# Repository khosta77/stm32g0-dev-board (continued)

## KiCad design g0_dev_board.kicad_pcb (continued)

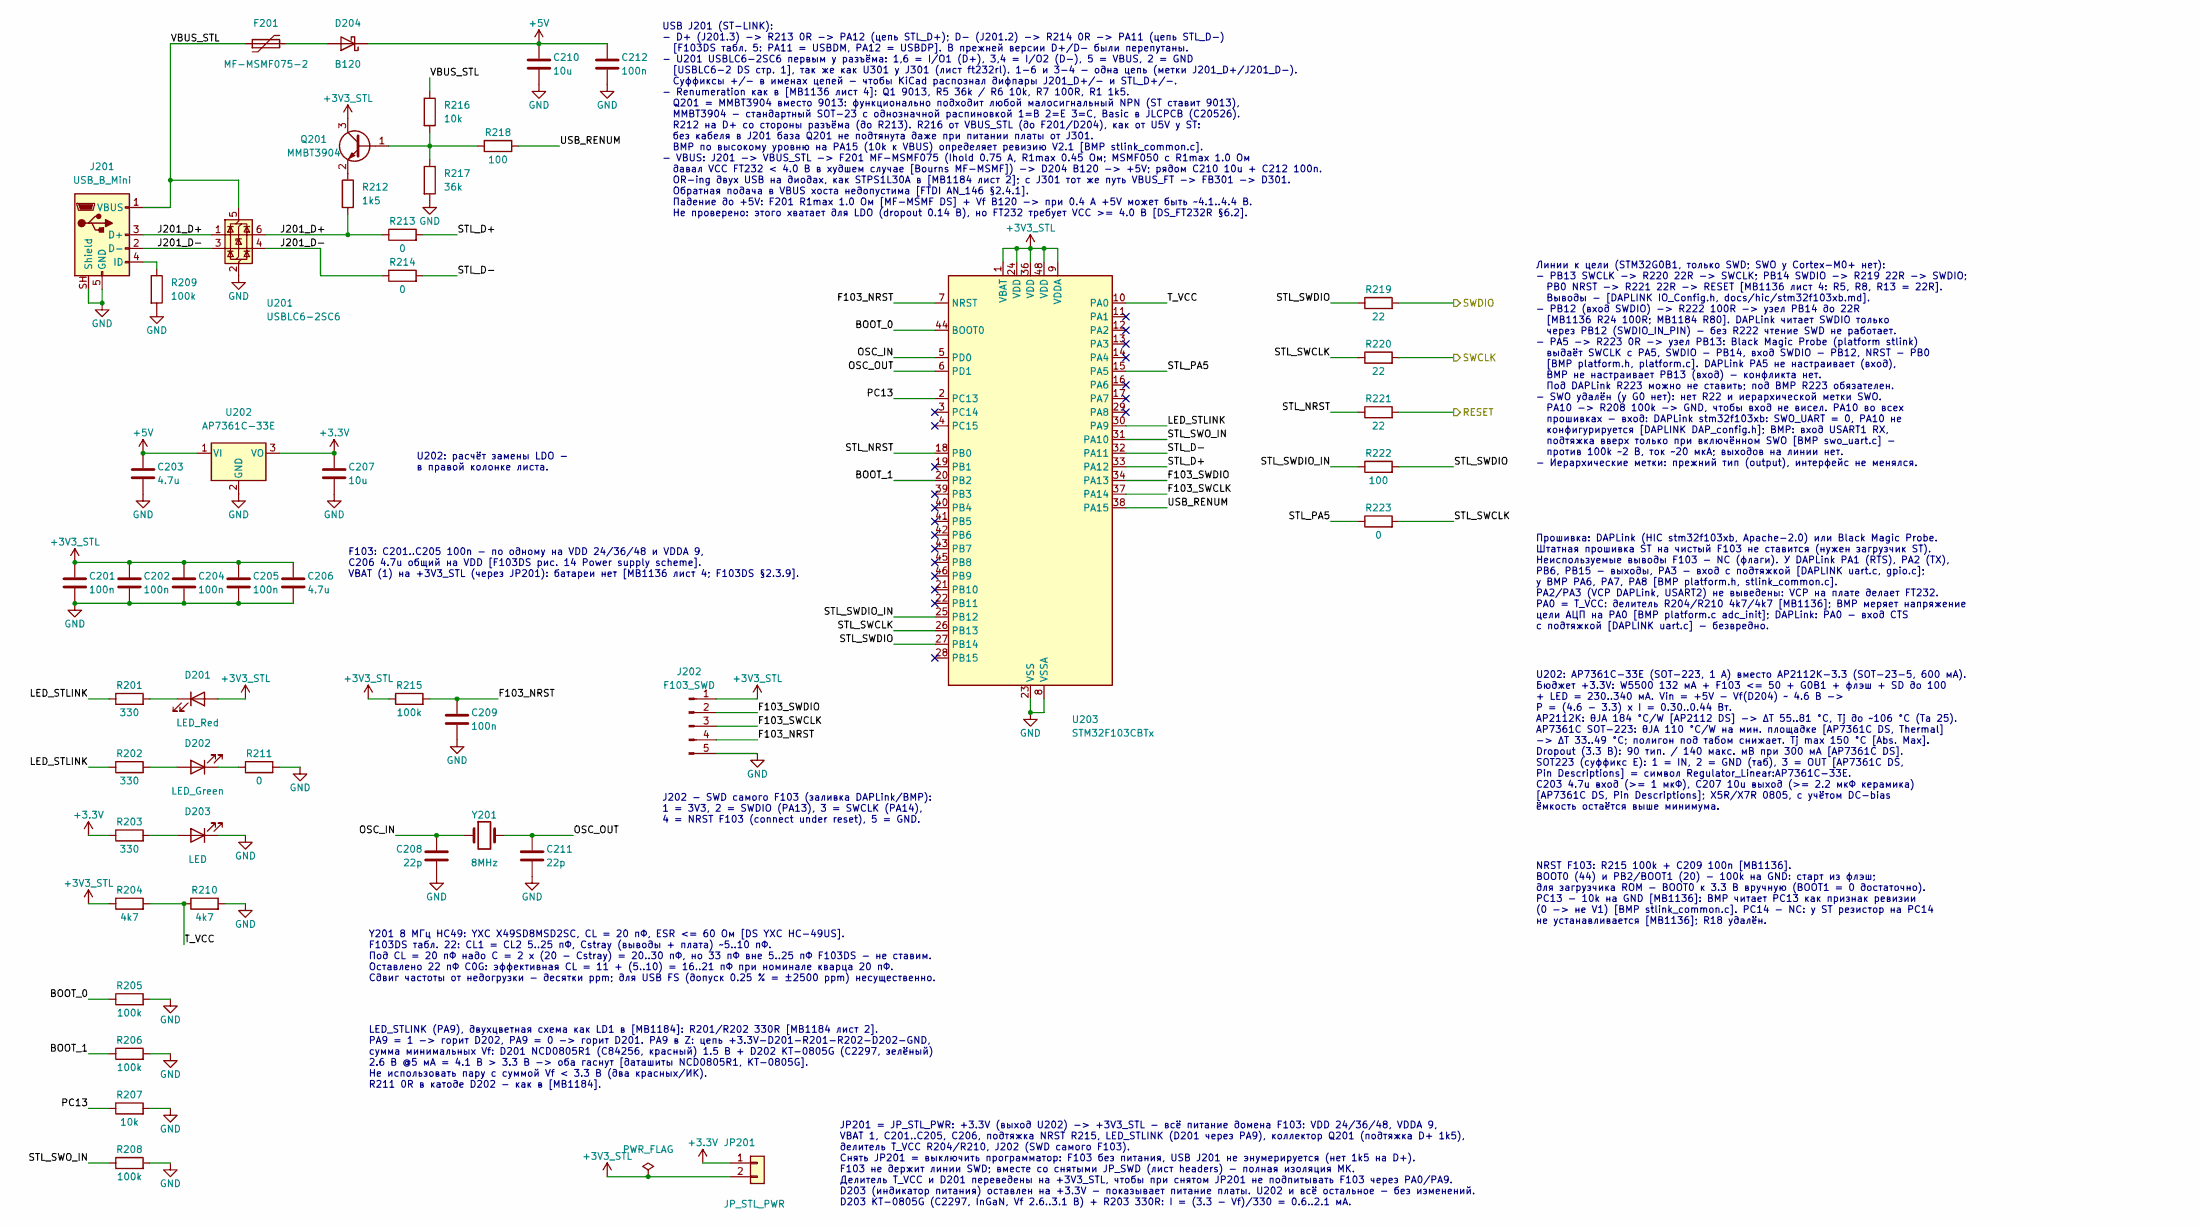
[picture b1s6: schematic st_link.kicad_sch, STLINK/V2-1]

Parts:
C201, C202, C204, C205, C209, C212: 100n; C_0805_2012Metric; LCSC C49678
C203, C206: 4.7u; C_0805_2012Metric; LCSC C1779
C207, C210: 10u; C_0805_2012Metric; LCSC C15850
C208, C211: 22p; C_0805_2012Metric; LCSC C1804
D201: LED_Red; LED_0805_2012Metric; LCSC C84256
D202: LED_Green; LED_0805_2012Metric; LCSC C2297
D203: LED; LED_0805_2012Metric; LCSC C2297
D204: B120; D_SMA; MPN B120-13-F; LCSC C134421
F201: MF-MSMF075-2; Fuse_1812_4532Metric; MPN MF-MSMF075-2; LCSC C84140
J201: USB_B_Mini; USB_Mini-B_Lumberg_2486_01_Horizontal
J202: F103_SWD; PinHeader_1x05_P2.54mm_Vertical; LCSC C42431835
JP201: JP_STL_PWR; PinHeader_1x02_P2.54mm_Vertical; LCSC C42431798
Q201: MMBT3904; SOT-23; LCSC C20526
R201, R202, R203: 330; R_0805_2012Metric; LCSC C17630
R204, R210: 4k7; R_0805_2012Metric; LCSC C17673
R205, R206, R208, R209, R215: 100k; R_0805_2012Metric; LCSC C149504
R207, R216: 10k; R_0805_2012Metric; LCSC C17414
R211, R213, R214, R223: 0; R_0805_2012Metric; LCSC C17477
R212: 1k5; R_0805_2012Metric; LCSC C4310
R217: 36k; R_0805_2012Metric; LCSC C4360
R218, R222: 100; R_0805_2012Metric; LCSC C17408
R219, R220, R221: 22; R_0805_2012Metric; LCSC C17561
U201: USBLC6-2SC6; SOT-23-6; MPN USBLC6-2SC6; LCSC C7519
U202: AP7361C-33E; SOT-223-3_TabPin2; MPN AP7361C-33E-13; LCSC C500795
U203: STM32F103CBTx; LQFP-48_7x7mm_P0.5mm; MPN STM32F103CBT6; LCSC C8304
Y201: 8MHz; Crystal_HC49-4H_Vertical; MPN X49SD8MSD2SC; LCSC C21263

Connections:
+3.3V: C207.1, JP201.1, R203.1, U202.3 (VO); also elsewhere on the board
+3V3_STL: C201.1, C202.1, C204.1, C205.1, C206.1, D201.2 (A), J202.1, JP201.2, Q201.3 (C), R204.1, R215.1, U203.1 (VBAT), U203.9 (VDDA), U203.24 (VDD), U203.36 (VDD), U203.48 (VDD)
+5V: C203.1, C210.1, C212.1, D204.1 (K), U202.1 (VI); also elsewhere on the board
/STL_RESET: R221.2; also elsewhere on the board
/STL_SWCLK: R220.2; also elsewhere on the board
/STL_SWDIO: R219.2; also elsewhere on the board
/st_link/BOOT_0: R205.1, U203.44 (BOOT0)
/st_link/BOOT_1: R206.1, U203.20 (PB2)
/st_link/F103_NRST: C209.1, J202.4, R215.2, U203.7 (NRST)
/st_link/F103_SWCLK: J202.3, U203.37 (PA14)
/st_link/F103_SWDIO: J202.2, U203.34 (PA13)
/st_link/J201_D+: J201.3 (D+), R212.2, R213.1, U201.1 (I/O1), U201.6 (I/O1)
/st_link/J201_D-: J201.2 (D-), R214.1, U201.3 (I/O2), U201.4 (I/O2)
/st_link/LED_STLINK: R201.1, R202.1, U203.30 (PA9)
/st_link/OSC_IN: C208.1, U203.5 (PD0), Y201.1
/st_link/OSC_OUT: C211.1, U203.6 (PD1), Y201.2
/st_link/PC13: R207.1, U203.2 (PC13)
/st_link/STL_D+: R213.2, U203.33 (PA12)
/st_link/STL_D-: R214.2, U203.32 (PA11)
/st_link/STL_NRST: R221.1, U203.18 (PB0)
/st_link/STL_PA5: R223.1, U203.15 (PA5)
/st_link/STL_SWCLK: R220.1, R223.2, U203.26 (PB13)
/st_link/STL_SWDIO: R219.1, R222.2, U203.27 (PB14)
/st_link/STL_SWDIO_IN: R222.1, U203.25 (PB12)
/st_link/STL_SWO_IN: R208.1, U203.31 (PA10)
/st_link/T_VCC: R204.2, R210.1, U203.10 (PA0)
/st_link/USB_RENUM: R218.2, U203.38 (PA15)
/st_link/VBUS_STL: F201.1, J201.1 (VBUS), R216.1, U201.5 (VBUS)
GND: C201.2, C202.2, C203.2, C204.2, C205.2, C206.2, C207.2, C208.2, C209.2, C210.2, C211.2, C212.2, D203.1 (K), J201.5 (GND), J201.SH (Shield), J202.5, R205.2, R206.2, R207.2, R208.2, R209.2, R210.2, R211.2, R217.2, U201.2 (GND), U202.2 (GND), U203.8 (VSSA), U203.23 (VSS), U203.35 (VSS), U203.47 (VSS); also elsewhere on the board
unnamed: D201.1 (K), R201.2
unnamed: D202.2 (A), R202.2
unnamed: D202.1 (K), R211.1
unnamed: D203.2 (A), R203.2
unnamed: D204.2 (A), F201.2
unnamed: J201.4 (ID), R209.1
unnamed: Q201.1 (B), R216.2, R217.1, R218.1
unnamed: Q201.2 (E), R212.1

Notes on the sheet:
F103: C201..C205 100n - по одному на VDD 24/36/48 и VDDA 9, C206 4.7u общий на VDD [F103DS рис. 14 Power supply scheme]. VBAT (1) на +3V3_STL (через JP201): батареи нет [MB1136 лист 4; F103DS §2.3.9].
Линии к цели (STM32G0B1, только SWD; SWO у Cortex-M0+ нет): - PB13 SWCLK -> R220 22R -> SWCLK; PB14 SWDIO -> R219 22R -> SWDIO; PB0 NRST -> R221 22R -> RESET [MB1136 лист 4: R5, R8, R13 = 22R]. Выводы - [DAPLINK IO_Config.h, docs/hic/stm32f103xb.md]. - PB12 (вход SWDIO) -> R222 100R -> узел PB14 до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
Y201 8 МГц HC49: YXC X49SD8MSD2SC, CL = 20 пФ, ESR <= 60 Ом [DS YXC HC-49US]. F103DS табл. 22: CL1 = CL2 5..25 пФ, Cstray (выводы + плата) ~5..10 пФ. Под CL = 20 пФ надо C = 2 x (20 - Cstray) = 20..30 пФ, но 33 пФ вне 5..25 пФ F103DS - не ставим. Оставлено 22 пФ C0G: эффективная CL = 11 + (5..10) =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
U202: расчёт замены LDO - в правой колонке листа.
JP201 = JP_STL_PWR: +3.3V (выход U202) -> +3V3_STL - всё питание домена F103: VDD 24/36/48, VDDA 9, VBAT 1, C201..C205, C206, подтяжка NRST R215, LED_STLINK (D201 через PA9), коллектор Q201 (подтяжка D+ 1k5), делитель T_VCC R204/R210, J202 (SWD самого F103). Снять JP201 = выключить программатор: F1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
U202: AP7361C-33E (SOT-223, 1 А) вместо AP2112K-3.3 (SOT-23-5, 600 мА). Бюджет +3.3V: W5500 132 мА + F103 <= 50 + G0B1 + флэш + SD до 100 + LED = 230..340 мА. Vin = +5V - Vf(D204) ~ 4.6 В -> P = (4.6 - 3.3) x I = 0.30..0.44 Вт. AP2112K: θJA 184 °C/W [AP2112 DS] -> ΔT 55..81 °C, Tj до ~106 °C (Ta 25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
NRST F103: R215 100k + C209 100n [MB1136]. BOOT0 (44) и PB2/BOOT1 (20) - 100k на GND: старт из флэш; для загрузчика ROM - BOOT0 к 3.3 В вручную (BOOT1 = 0 достаточно). PC13 - 10k на GND [MB1136]: BMP читает PC13 как признак ревизии (0 -> не V1) [BMP stlink_common.c]. PC14 - NC: у ST резистор на PC1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
Прошивка: DAPLink (HIC stm32f103xb, Apache-2.0) или Black Magic Probe. Штатная прошивка ST на чистый F103 не ставится (нужен загрузчик ST). Неиспользуемые выводы F103 - NC (флаги). У DAPLink PA1 (RTS), PA2 (TX), PB6, PB15 - выходы, PA3 - вход с подтяжкой [DAPLINK uart.c, gpio.c]; у BMP PA6, PA7, PA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
J202 - SWD самого F103 (заливка DAPLink/BMP): 1 = 3V3, 2 = SWDIO (PA13), 3 = SWCLK (PA14), 4 = NRST F103 (connect under reset), 5 = GND.
USB J201 (ST-LINK): - D+ (J201.3) -> R213 0R -> PA12 (цепь STL_D+); D- (J201.2) -> R214 0R -> PA11 (цепь STL_D-) [F103DS табл. 5: PA11 = USBDM, PA12 = USBDP]. В прежней версии D+/D- были перепутаны. - U201 USBLC6-2SC6 первым у разъёма: 1,6 = I/O1 (D+), 3,4 = I/O2 (D-), 5 = VBUS, 2 = GND [USBLC6-2 D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
LED_STLINK (PA9), двухцветная схема как LD1 в [MB1184]: R201/R202 330R [MB1184 лист 2]. PA9 = 1 -> горит D202, PA9 = 0 -> горит D201. PA9 в Z: цепь +3.3V-D201-R201-R202-D202-GND, сумма минимальных Vf: D201 NCD0805R1 (C84256, красный) 1.5 В + D202 KT-0805G (C2297, зелёный) 2.6 В @5 мА = 4.1 В > 3.3 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

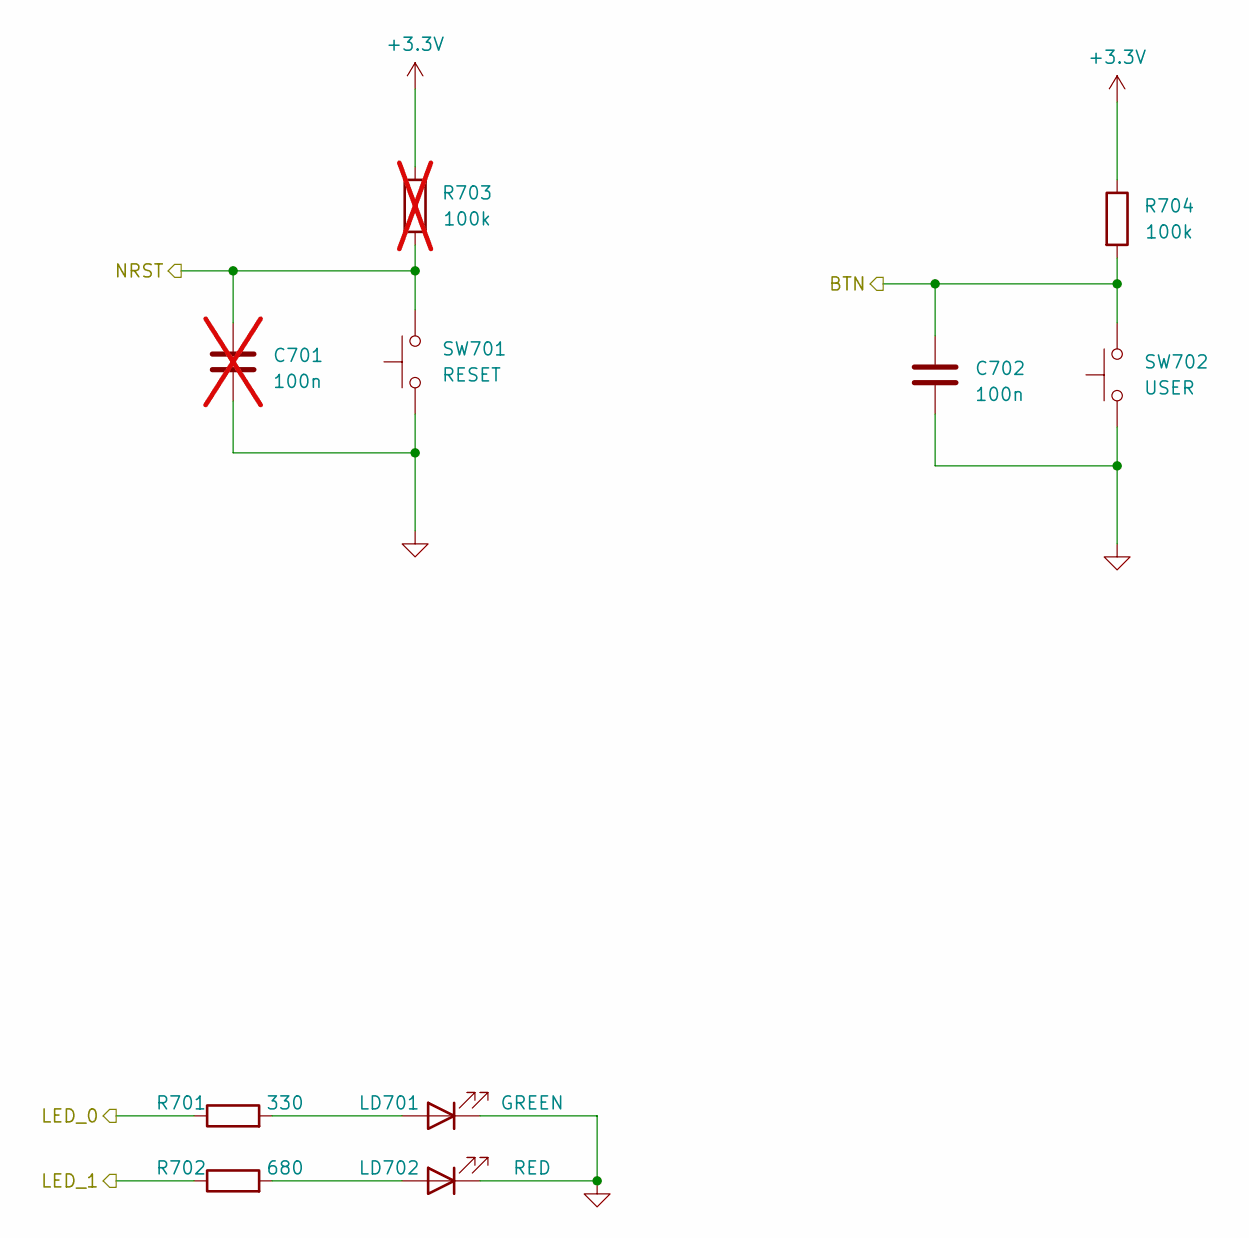
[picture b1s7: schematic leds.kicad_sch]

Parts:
C701: 100n; C_0805_2012Metric; LCSC C49678; not fitted
C702: 100n; C_0805_2012Metric; LCSC C49678
LD701: GREEN; LED_0805_2012Metric; LCSC C2297
LD702: RED; LED_0805_2012Metric; LCSC C84256
R701: 330; R_0805_2012Metric; LCSC C17630
R702: 680; R_0805_2012Metric; LCSC C17798
R703: 100k; R_0805_2012Metric; LCSC C149504; not fitted
R704: 100k; R_0805_2012Metric; LCSC C149504
SW701: RESET; SW_SPST_PTS645Sx43SMTR92; LCSC C221880
SW702: USER; SW_SPST_PTS645Sx43SMTR92; LCSC C221880

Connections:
+3.3V: R703.1, R704.1; also elsewhere on the board
/BTN: C702.2, R704.2, SW702.2; also elsewhere on the board
/LED0: R701.1; also elsewhere on the board
/LED1: R702.1; also elsewhere on the board
/NRST: C701.2, R703.2, SW701.2; also elsewhere on the board
GND: C701.1, C702.1, LD701.1 (K), LD702.1 (K), SW701.1, SW702.1; also elsewhere on the board
unnamed: LD701.2 (A), R701.2
unnamed: LD702.2 (A), R702.2

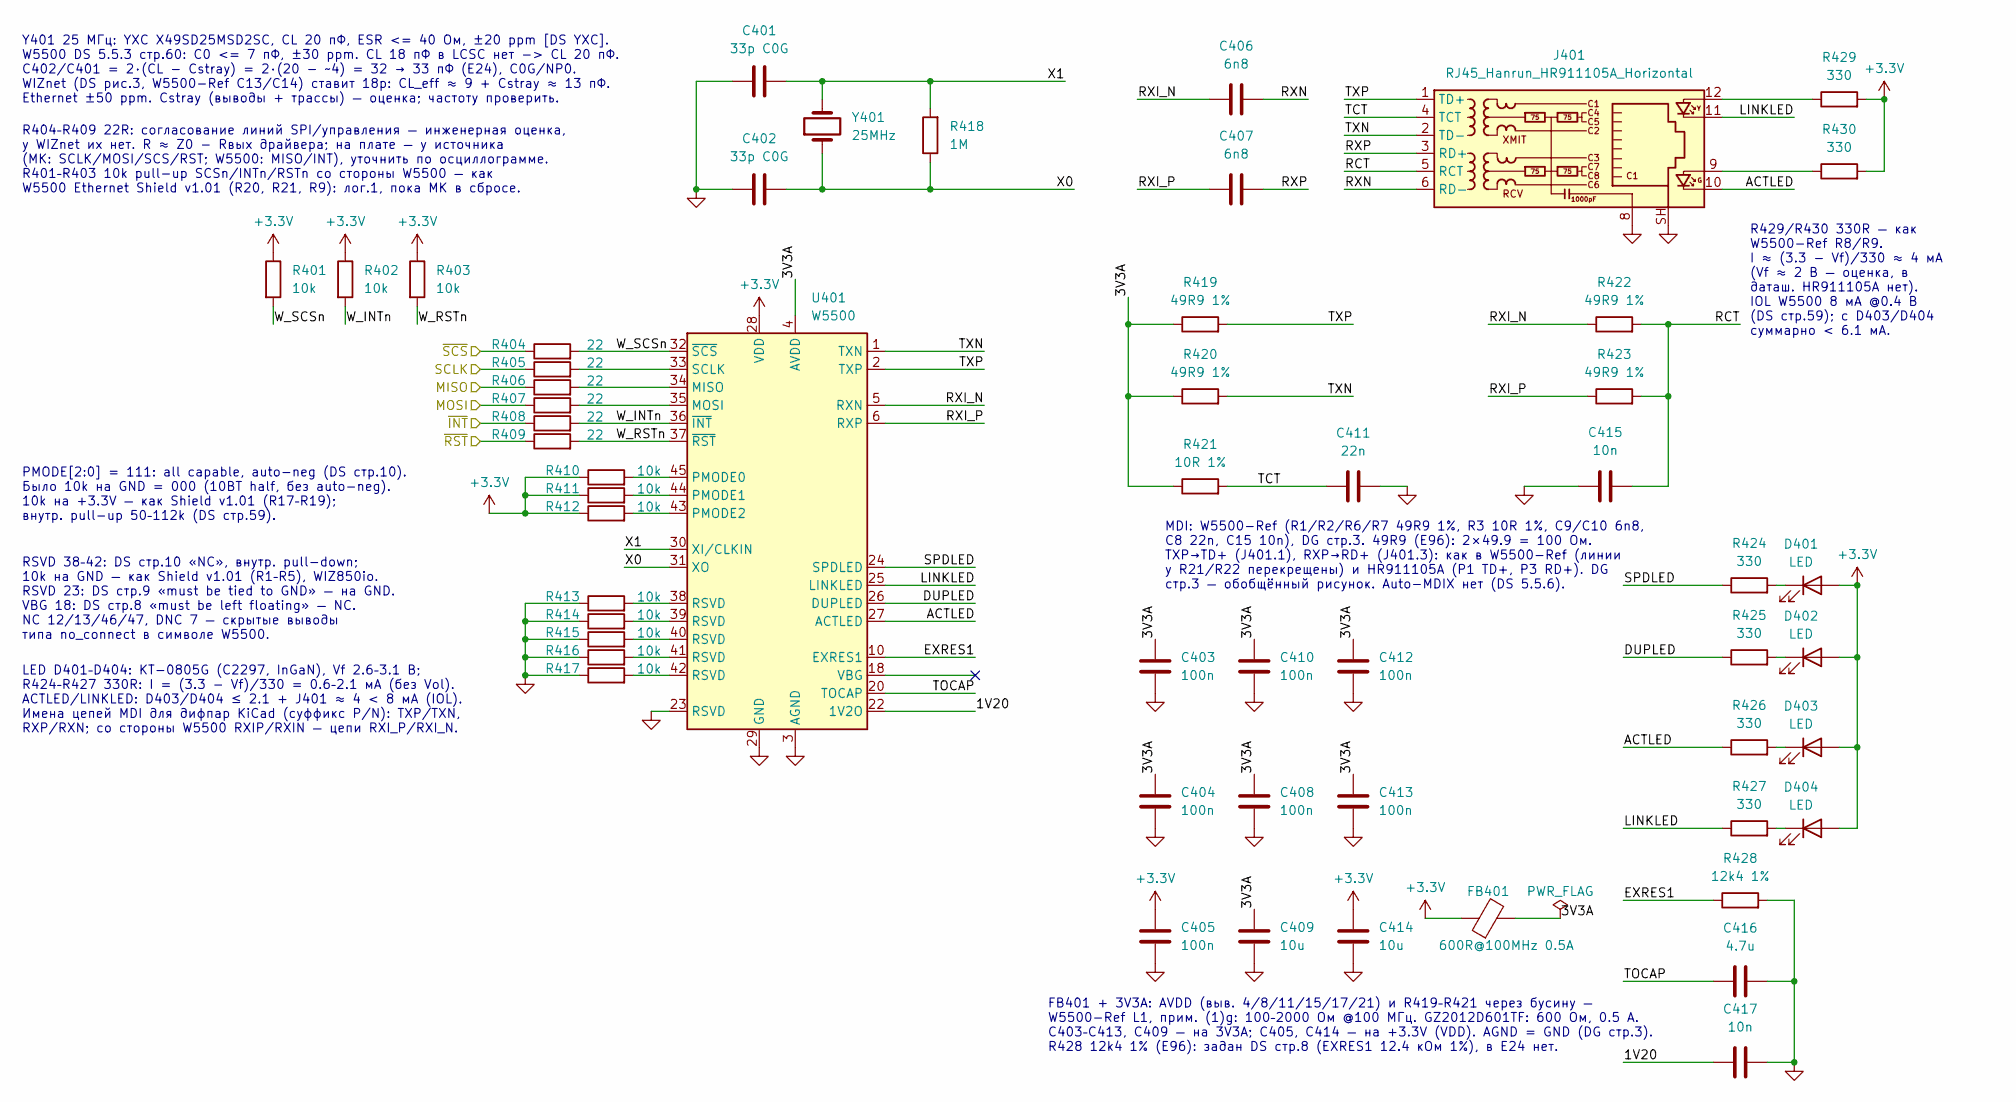
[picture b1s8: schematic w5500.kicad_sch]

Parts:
C401, C402: 33p C0G; C_0805_2012Metric; LCSC C157687
C403, C404, C405, C408, C410, C412, C413: 100n; C_0805_2012Metric; LCSC C49678
C406, C407: 6n8; C_0805_2012Metric; LCSC C1755
C409, C414: 10u; C_0805_2012Metric; LCSC C15850
C411: 22n; C_0805_2012Metric; LCSC C1729
C415, C417: 10n; C_0805_2012Metric; LCSC C1710
C416: 4.7u; C_0805_2012Metric; LCSC C1779
D401, D402, D403, D404: LED; LED_0805_2012Metric; LCSC C2297
FB401: 600R@100MHz 0.5A; L_0805_2012Metric; MPN GZ2012D601TF; LCSC C1017
J401: RJ45_Hanrun_HR911105A_Horizontal; LCSC C12074
R401, R402, R403, R410, R411, R412, R413, R414, R415, R416, R417: 10k; R_0805_2012Metric; LCSC C17414
R404, R405, R406, R407, R408, R409: 22; R_0805_2012Metric; LCSC C17561
R418: 1M; R_0805_2012Metric; LCSC C17514
R419, R420, R422, R423: 49R9 1%; R_0805_2012Metric; LCSC C17720
R421: 10R 1%; R_0805_2012Metric; LCSC C17415
R424, R425, R426, R427, R429, R430: 330; R_0805_2012Metric; LCSC C17630
R428: 12k4 1%; R_0805_2012Metric; LCSC C30908
U401: W5500; LQFP-48_7x7mm_P0.5mm; LCSC C32843
Y401: 25MHz; Crystal_HC49-4H_Vertical; MPN X49SD25MSD2SC; LCSC C14730

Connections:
+3.3V: C405.1, C414.1, D401.2 (A), D402.2 (A), D403.2 (A), D404.2 (A), FB401.1, R401.1, R402.1, R403.1, R410.1, R411.1, R412.1, R429.2, R430.2, U401.28 (VDD); also elsewhere on the board
/SPI2_MISO: R406.1; also elsewhere on the board
/SPI2_MOSI: R407.1; also elsewhere on the board
/SPI2_SCK: R405.1; also elsewhere on the board
/W_CS: R404.1; also elsewhere on the board
/W_INT: R408.1; also elsewhere on the board
/W_RST: R409.1; also elsewhere on the board
/w5500/1V20: C417.1, U401.22 (1V2O)
/w5500/3V3A: C403.1, C404.1, C408.1, C409.1, C410.1, C412.1, C413.1, FB401.2, R419.1, R420.1, R421.1, U401.4 (AVDD), U401.8 (AVDD), U401.11 (AVDD), U401.15 (AVDD), U401.17 (AVDD), U401.21 (AVDD)
/w5500/ACTLED: J401.10, R426.1, U401.27 (ACTLED)
/w5500/DUPLED: R425.1, U401.26 (DUPLED)
/w5500/EXRES1: R428.1, U401.10 (EXRES1)
/w5500/LINKLED: J401.11, R427.1, U401.25 (LINKLED)
/w5500/RCT: C415.2, J401.5 (RCT), R422.2, R423.2
/w5500/RXI_N: C406.1, R422.1, U401.5 (RXN)
/w5500/RXI_P: C407.1, R423.1, U401.6 (RXP)
/w5500/RXN: C406.2, J401.6 (RD-)
/w5500/RXP: C407.2, J401.3 (RD+)
/w5500/SPDLED: R424.1, U401.24 (SPDLED)
/w5500/TCT: C411.1, J401.4 (TCT), R421.2
/w5500/TOCAP: C416.1, U401.20 (TOCAP)
/w5500/TXN: J401.2 (TD-), R420.2, U401.1 (TXN)
/w5500/TXP: J401.1 (TD+), R419.2, U401.2 (TXP)
/w5500/W_INTn: R402.2, R408.2, U401.36 (~INT)
/w5500/W_RSTn: R403.2, R409.2, U401.37 (~RST)
/w5500/W_SCSn: R401.2, R404.2, U401.32 (~SCS)
/w5500/X0: C402.2, R418.1, U401.31 (XO), Y401.1
/w5500/X1: C401.2, R418.2, U401.30 (XI/CLKIN), Y401.2
GND: C401.1, C402.1, C403.2, C404.2, C405.2, C408.2, C409.2, C410.2, C411.2, C412.2, C413.2, C414.2, C415.1, C416.2, C417.2, J401.8, J401.SH, R413.1, R414.1, R415.1, R416.1, R417.1, R428.2, U401.3 (AGND), U401.9 (AGND), U401.14 (AGND), U401.16 (AGND), U401.19 (AGND), U401.23 (RSVD), U401.29 (GND), U401.48 (AGND); also elsewhere on the board
unnamed: D401.1 (K), R424.2
unnamed: D402.1 (K), R425.2
unnamed: D403.1 (K), R426.2
unnamed: D404.1 (K), R427.2
unnamed: J401.9, R430.1
unnamed: J401.12, R429.1
unnamed: R413.2, U401.38 (RSVD)
unnamed: R414.2, U401.39 (RSVD)
unnamed: R415.2, U401.40 (RSVD)
unnamed: R416.2, U401.41 (RSVD)
unnamed: R417.2, U401.42 (RSVD)
unnamed: R406.2, U401.34 (MISO)
unnamed: R407.2, U401.35 (MOSI)
unnamed: R410.2, U401.45 (PMODE0)
unnamed: R411.2, U401.44 (PMODE1)
unnamed: R412.2, U401.43 (PMODE2)
unnamed: R405.2, U401.33 (SCLK)

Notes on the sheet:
R404–R409 22R: согласование линий SPI/управления — инженерная оценка, у WIZnet их нет. R ≈ Z0 − Rвых драйвера; на плате — у источника (МК: SCLK/MOSI/SCS/RST; W5500: MISO/INT), уточнить по осциллограмме. R401–R403 10k pull-up SCSn/INTn/RSTn со стороны W5500 — как W5500 Ethernet Shield v1.01 (R20, R2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
RSVD 38–42: DS стр.10 «NC», внутр. pull-down; 10k на GND — как Shield v1.01 (R1–R5), WIZ850io. RSVD 23: DS стр.9 «must be tied to GND» — на GND. VBG 18: DS стр.8 «must be left floating» — NC. NC 12/13/46/47, DNC 7 — скрытые выводы типа no_connect в символе W5500.
LED D401–D404: KT-0805G (C2297, InGaN), Vf 2.6–3.1 В; R424–R427 330R: I = (3.3 − Vf)/330 = 0.6–2.1 мА (без Vol). ACTLED/LINKLED: D403/D404 ≤ 2.1 + J401 ≈ 4 < 8 мА (IOL). Имена цепей MDI для дифпар KiCad (суффикс P/N): TXP/TXN, RXP/RXN; со стороны W5500 RXIP/RXIN — цепи RXI_P/RXI_N.
MDI: W5500-Ref (R1/R2/R6/R7 49R9 1%, R3 10R 1%, C9/C10 6n8, C8 22n, C15 10n), DG стр.3. 49R9 (E96): 2×49.9 = 100 Ом. TXP→TD+ (J401.1), RXP→RD+ (J401.3): как в W5500-Ref (линии у R21/R22 перекрещены) и HR911105A (P1 TD+, P3 RD+). DG стр.3 — обобщённый рисунок. Auto-MDIX нет (DS 5.5.6).
Y401 25 МГц: YXC X49SD25MSD2SC, CL 20 пФ, ESR <= 40 Ом, ±20 ppm [DS YXC]. W5500 DS 5.5.3 стр.60: C0 <= 7 пФ, ±30 ppm. CL 18 пФ в LCSC нет -> CL 20 пФ. C402/C401 = 2·(CL − Cstray) = 2·(20 − ~4) = 32 → 33 пФ (E24), C0G/NP0. WIZnet (DS рис.3, W5500-Ref C13/C14) ставит 18p: CL_eff ≈ 9 + Cstray ≈ 13 пФ.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
PMODE[2:0] = 111: all capable, auto-neg (DS стр.10). Было 10k на GND = 000 (10BT half, без auto-neg). 10k на +3.3V — как Shield v1.01 (R17–R19); внутр. pull-up 50–112k (DS стр.59).
R429/R430 330R — как W5500-Ref R8/R9. I ≈ (3.3 − Vf)/330 ≈ 4 мА (Vf ≈ 2 В — оценка, в даташ. HR911105A нет). IOL W5500 8 мА @0.4 В (DS стр.59); с D403/D404 суммарно < 6.1 мА.
FB401 + 3V3A: AVDD (выв. 4/8/11/15/17/21) и R419–R421 через бусину — W5500-Ref L1, прим. (1)g: 100–2000 Ом @100 МГц. GZ2012D601TF: 600 Ом, 0.5 А. C403–C413, C409 — на 3V3A; C405, C414 — на +3.3V (VDD). AGND = GND (DG стр.3). R428 12k4 1% (E96): задан DS стр.8 (EXRES1 12.4 кОм 1%), в E24 нет.

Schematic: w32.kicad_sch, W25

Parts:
C501: 100n X7R; C_0805_2012Metric; LCSC C49678
C502, C504: 10u; C_0805_2012Metric; LCSC C15850
C503, C505: 100n; C_0805_2012Metric; LCSC C49678
J501: DM3AT-SF-PEJM5; microSD_HC_Hirose_DM3AT-SF-PEJM5; MPN DM3AT-SF-PEJM5; LCSC C114218
R501, R502, R503, R504, R507, R508, R509, R510: 10; R_0805_2012Metric; LCSC C17415
R505, R511, R516, R517: 10k; R_0805_2012Metric; LCSC C17414
R506, R512, R513, R514, R515: 47k; R_0805_2012Metric; LCSC C17713
U501: W25Q32JVSSIQ; SOIC-8_5.3x5.3mm_P1.27mm; MPN W25Q32JVSSIQ; LCSC C179173

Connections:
+3.3V: C501.1, C502.1, C503.1, C504.1, J501.4 (VDD), R505.1, R506.1, R511.1, R512.1, R513.1, R514.1, R515.1, R516.1, R517.1, U501.8 (VCC); also elsewhere on the board
/CARD_DET: C505.1, J501.10 (DET_A), R506.2; also elsewhere on the board
/FL_CS: R501.1; also elsewhere on the board
/SD_CS: R507.1; also elsewhere on the board
/SPI2_MISO: R504.1, R510.1; also elsewhere on the board
/SPI2_MOSI: R503.1, R508.1; also elsewhere on the board
/SPI2_SCK: R502.1, R509.1; also elsewhere on the board
/w32/SD_CMD: J501.3 (CMD), R508.2, R512.2
/w32/SD_DAT0: J501.7 (DAT0), R510.2, R513.2
/w32/SD_DAT1: J501.8 (DAT1), R514.2
/w32/SD_DAT2: J501.1 (DAT2), R515.2
/w32/SD_DAT3: J501.2 (DAT3/CD), R507.2, R511.2
GND: C501.2, C502.2, C503.2, C504.2, C505.2, J501.6 (VSS), J501.9 (DET_B), J501.SH (SHIELD), U501.4 (GND); also elsewhere on the board
unnamed: J501.5 (CLK), R509.2
unnamed: R502.2, U501.6 (CLK)
unnamed: R503.2, U501.5 (DI/IO_{0})
unnamed: R504.2, U501.2 (DO/IO_{1})
unnamed: R501.2, R505.2, U501.1 (~CS)
unnamed: R517.2, U501.7 (~HOLD/~RESET/IO_{3})
unnamed: R516.2, U501.3 (~WP/IO_{2})

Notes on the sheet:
Подтяжки SD на +3.3V со стороны J501 (после 10 Ом): CMD, DAT0, DAT1, DAT2 — 47k; DAT3/CS — 10k (карта не выбрана, пока выводы МК в Hi-Z). DAT1/DAT2 в SPI не используются, но не должны плавать. NXP AN10911 Табл. 3: RCMD, RDAT = 10–100 кОм; Adafruit 4682: 47k. Номинал спорный: ESP-IDF (sd_pullup_requ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
U501 W25Q32JVSSIQ (было W25Q128JVS): 4 МиБ, JEDEC ID EF4016 — как в драйвере SDK w25q32.cppm; Renode GenericSpiFlash без правок. На то же место: W25Q64JVSSIQ, W25Q128JVSIQ. Только суффикс IQ/JQ: QE=1 заводской (DS W25Q32JV Rev G §7.1, бит QE) — /WP и /HOLD отключены. Выв. 3 и 7 — через R516, R517 1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
J501: символ Micro_SD_Card_Det_Hirose_DM3AT под footprint DM3AT-SF-PEJM5: пл. 9 = DET_B, 10 = DET_A, SH = корпус. Было: Micro_SD_Card, выв. 9 «SHIELD» на GND — это контакт детекта. Детект нормально разомкнут (каталог Hirose DM3, п. 5): DET_B = GND, DET_A = /CARD_DET + 47k (R506) на +3.3V; /CARD_DET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
R505 10k: /CS следует за VCC при вкл./выкл., пока выводы МК в Hi-Z (DS W25Q32JV Rev G §4.1, §9.3 «/CS must track VCC»). C501 100n — вплотную к выв. 8 U501 (ВЧ-развязка; номинал в DS не задан, практика). C502 10u оставлен рядом как локальный запас по питанию U501.
C503 100n + C504 10u — у выв. 4 (VDD) J501; 10 мкФ + 0.1 мкФ как у Adafruit 4682 (C1, C2).
Прошивка (флэш и SD на одной шине SPI): 1) SD отпускает MISO только по тактам SCK: после подъёма CS_card послать 1 dummy-байт (ELM-ChaN, «How to Use MMC/SDC», раздел Multi-slave). 2) SD инициализировать до первых обращений к U501: CS_card=1, MOSI=1, ≥74 тактов SCK на 100–400 кГц, затем CMD0 при CS_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
C505 100n (у J501, /CARD_DET -> GND): антидребезг детекта карты, RC = 47k (R506) · 100n ≈ 4.7 мс. Необязателен при программной фильтрации /CARD_DET (инженерная оценка, не из DS).

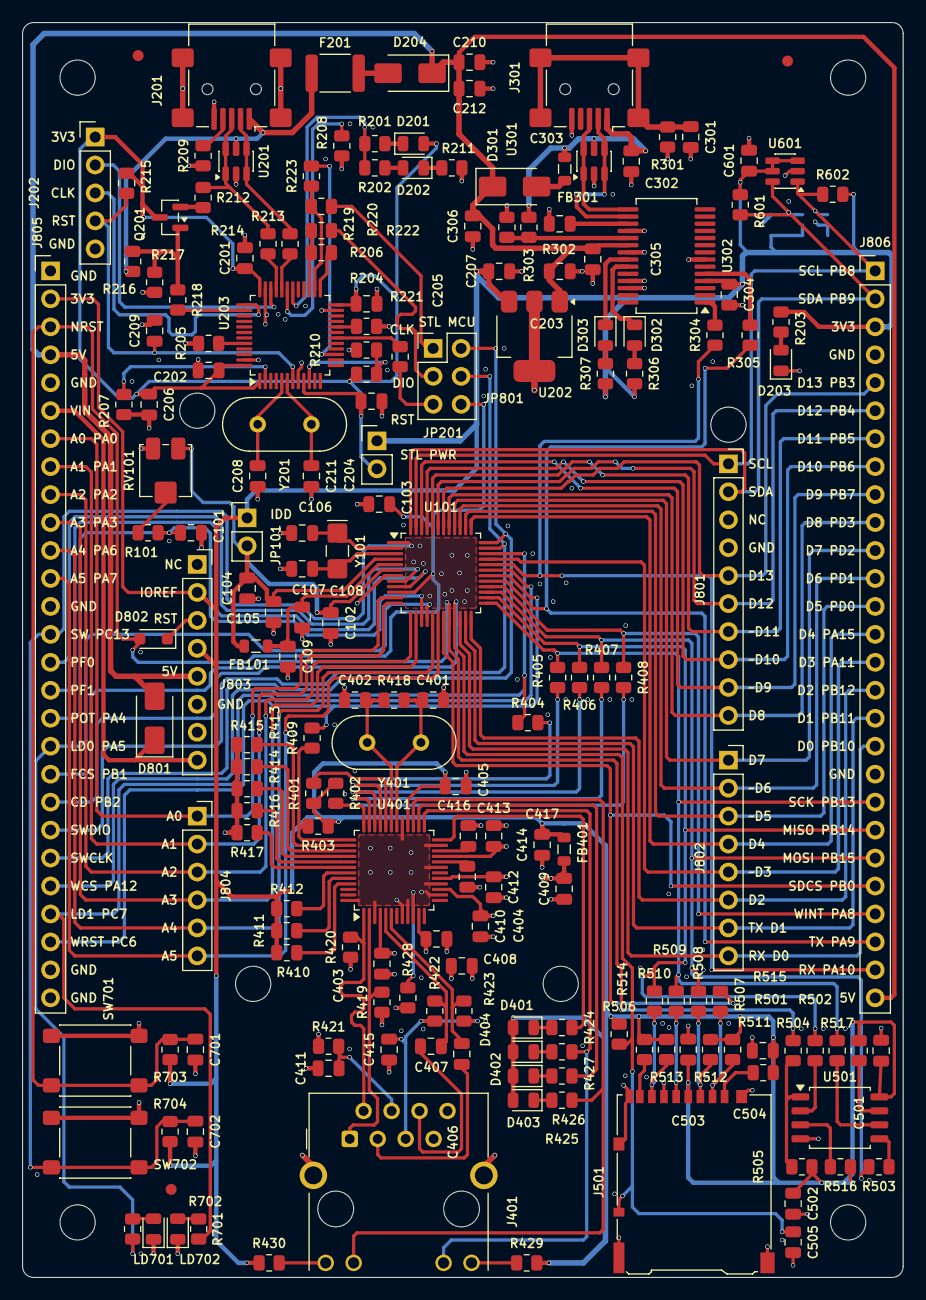
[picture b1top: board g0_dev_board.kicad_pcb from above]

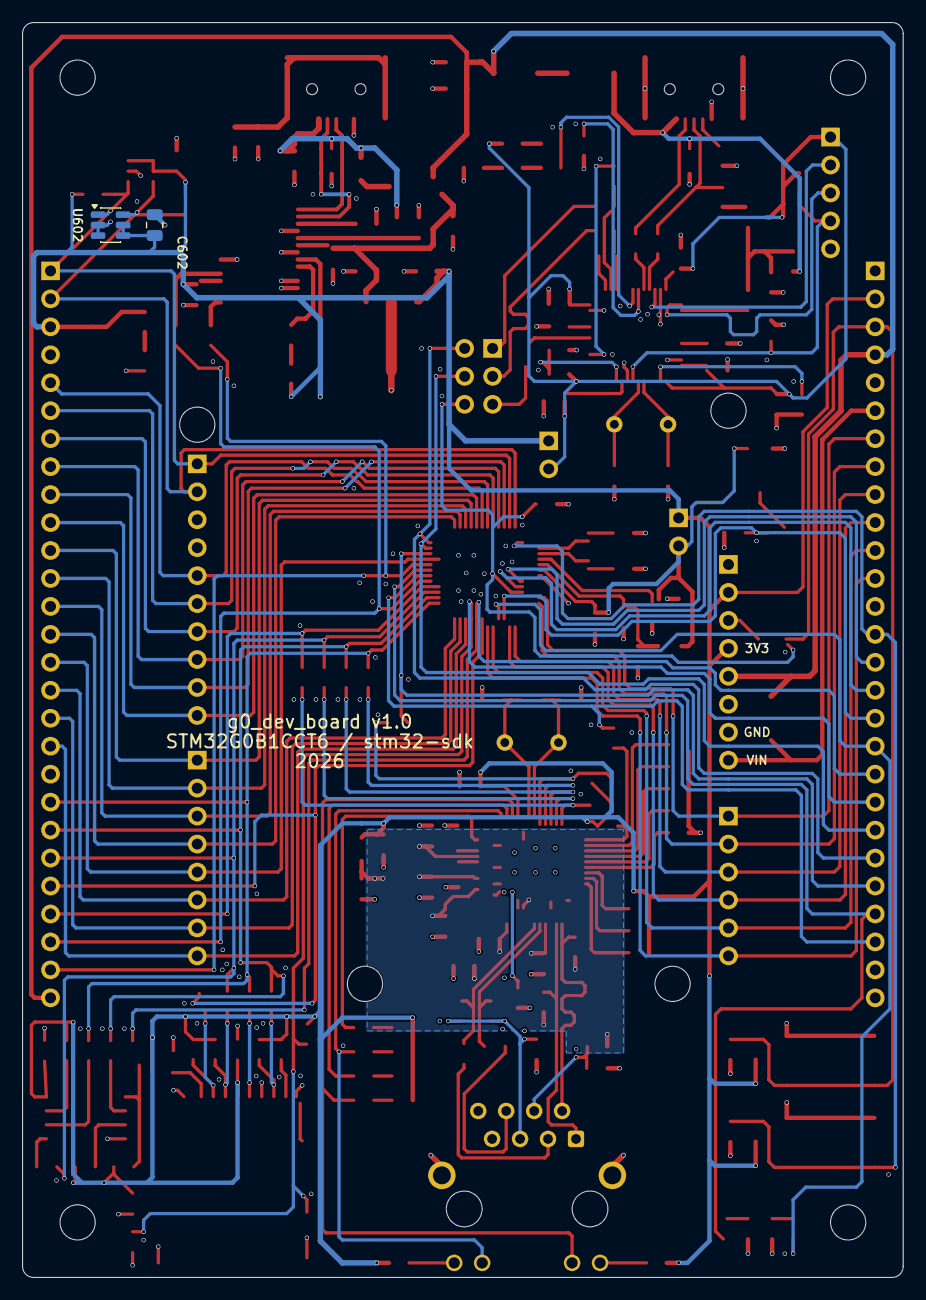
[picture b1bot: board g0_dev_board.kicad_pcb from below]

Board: 4 copper layers, 80.0 x 114.0 mm, 198 parts (2 on the bottom side), 151 nets.

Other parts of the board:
FID1, FID2, FID3: Fiducial_1mm_Mask2mm
H1, H2, H3, H4: MountingHole_3.2mm_M3
H801, H802, H803, H804: Arduino_MountingHole_3.2mm

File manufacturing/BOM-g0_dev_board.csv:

Comment,Designator,Footprint,LCSC Part #
100n,"C101,C102,C103,C105,C107,C201,C202,C204,C205,C209,C212,C303,C304,C305,C403,C404,C405,C408,C410,C412,C413,C503,C505,C702",C_0805_2012Metric,C49678
4.7u,"C104,C203,C206,C306,C416",C_0805_2012Metric,C1779
6.8p C0G,"C106,C108",C_0805_2012Metric,C1832
10u,"C207,C210,C409,C414,C502,C504",C_0805_2012Metric,C15850
22p,"C208,C211",C_0805_2012Metric,C1804
10n,"C302,C415,C417",C_0805_2012Metric,C1710
33p C0G,"C401,C402",C_0805_2012Metric,C157687
6n8,"C406,C407",C_0805_2012Metric,C1755
22n,C411,C_0805_2012Metric,C1729
100n X7R,"C501,C601,C602",C_0805_2012Metric,C49678
LED_Red,D201,LED_0805_2012Metric,C84256
LED_Green,D202,LED_0805_2012Metric,C2297
LED,"D203,D401,D402,D403,D404",LED_0805_2012Metric,C2297
B120,"D204,D301,D801",D_SMA,C134421
TX,D302,LED_0805_2012Metric,C2297
RX,D303,LED_0805_2012Metric,C2297
BAT54WS,D802,D_SOD-323_HandSoldering,C124205
MF-MSMF075-2,F201,Fuse_1812_4532Metric,C84140
600R@100MHz 0.5A,"FB101,FB401",L_0805_2012Metric,C1017
220R@100MHz 2A,FB301,L_0805_2012Metric,C85840
USB_B_Mini,"J201,J301",USB_Mini-B_Lumberg_2486_01_Horizontal,
F103_SWD,J202,PinHeader_1x05_P2.54mm_Vertical,C42431835
RJ45_Hanrun_HR911105A_Horizontal,J401,RJ45_Hanrun_HR911105A_Horizontal,C12074
DM3AT-SF-PEJM5,J501,microSD_HC_Hirose_DM3AT-SF-PEJM5,C114218
Uno_IOH,J801,PinSocket_1x10_P2.54mm_Vertical,C2905418
Uno_IOL,J802,PinSocket_1x08_P2.54mm_Vertical,C42431840
Uno_POWER,J803,PinSocket_1x08_P2.54mm_Vertical,C42431840
Uno_ANALOG,J804,PinSocket_1x06_P2.54mm_Vertical,C40877
J_LA_L,J805,PinHeader_1x27_P2.54mm_Vertical,
J_LA_R,J806,PinHeader_1x27_P2.54mm_Vertical,
JP_IDD,JP101,PinHeader_1x02_P2.54mm_Vertical,C42431798
JP_STL_PWR,JP201,PinHeader_1x02_P2.54mm_Vertical,C42431798
JP_SWD,JP801,PinHeader_2x03_P2.54mm_Vertical,
GREEN,LD701,LED_0805_2012Metric,C2297
RED,LD702,LED_0805_2012Metric,C84256
MMBT3904,Q201,SOT-23,C20526
1k,"R101,R302,R304,R305",R_0805_2012Metric,C17513
330,"R201,R202,R203,R306,R307,R424,R425,R426,R427,R429,R430,R701",R_0805_2012Metric,C17630
4k7,"R204,R210",R_0805_2012Metric,C17673
100k,"R205,R206,R208,R209,R215,R704",R_0805_2012Metric,C149504
10k,"R207,R216,R401,R402,R403,R410,R411,R412,R413,R414,R415,R416,R417,R505,R511,R516,R517",R_0805_2012Metric,C17414
0,"R211,R213,R214,R223,R301",R_0805_2012Metric,C17477
1k5,R212,R_0805_2012Metric,C4310
36k,R217,R_0805_2012Metric,C4360
100,"R218,R222",R_0805_2012Metric,C17408
22,"R219,R220,R221,R404,R405,R406,R407,R408,R409",R_0805_2012Metric,C17561
2.2k,R303,R_0805_2012Metric,C17520
1M,R418,R_0805_2012Metric,C17514
49R9 1%,"R419,R420,R422,R423",R_0805_2012Metric,C17720
10R 1%,R421,R_0805_2012Metric,C17415
12k4 1%,R428,R_0805_2012Metric,C30908
10,"R501,R502,R503,R504,R507,R508,R509,R510",R_0805_2012Metric,C17415
47k,"R506,R512,R513,R514,R515",R_0805_2012Metric,C17713
4.7k,"R601,R602",R_0805_2012Metric,C17673
680,R702,R_0805_2012Metric,C17798
10k,RV101,Potentiometer_Bourns_3314J_Vertical,C36376
RESET,SW701,SW_SPST_PTS645Sx43SMTR92,C221880
USER,SW702,SW_SPST_PTS645Sx43SMTR92,C221880
STM32G0B1CCT6,U101,LQFP-48_7x7mm_P0.5mm,C5270241
USBLC6-2SC6,"U201,U301",SOT-23-6,C7519
AP7361C-33E,U202,SOT-223-3_TabPin2,C500795
STM32F103CBTx,U203,LQFP-48_7x7mm_P0.5mm,C8304
FT232RL,U302,SSOP-28_5.3x10.2mm_P0.65mm,C8690
W5500,U401,LQFP-48_7x7mm_P0.5mm,C32843
W25Q32JVSSIQ,U501,SOIC-8_5.3x5.3mm_P1.27mm,C179173
TMP100,"U601,U602",SOT-23-6,C31810
32.768kHz CL7pF,Y101,Crystal_SMD_G8-2Pin_3.2x1.5mm_HandSoldering,C48615
8MHz,Y201,Crystal_HC49-4H_Vertical,C21263
25MHz,Y401,Crystal_HC49-4H_Vertical,C14730
